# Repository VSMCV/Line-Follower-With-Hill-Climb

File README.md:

# Line-Follower-With-Hill-Climb
Hardware design and software files for a PID line follower robot with Hill Climb tuning

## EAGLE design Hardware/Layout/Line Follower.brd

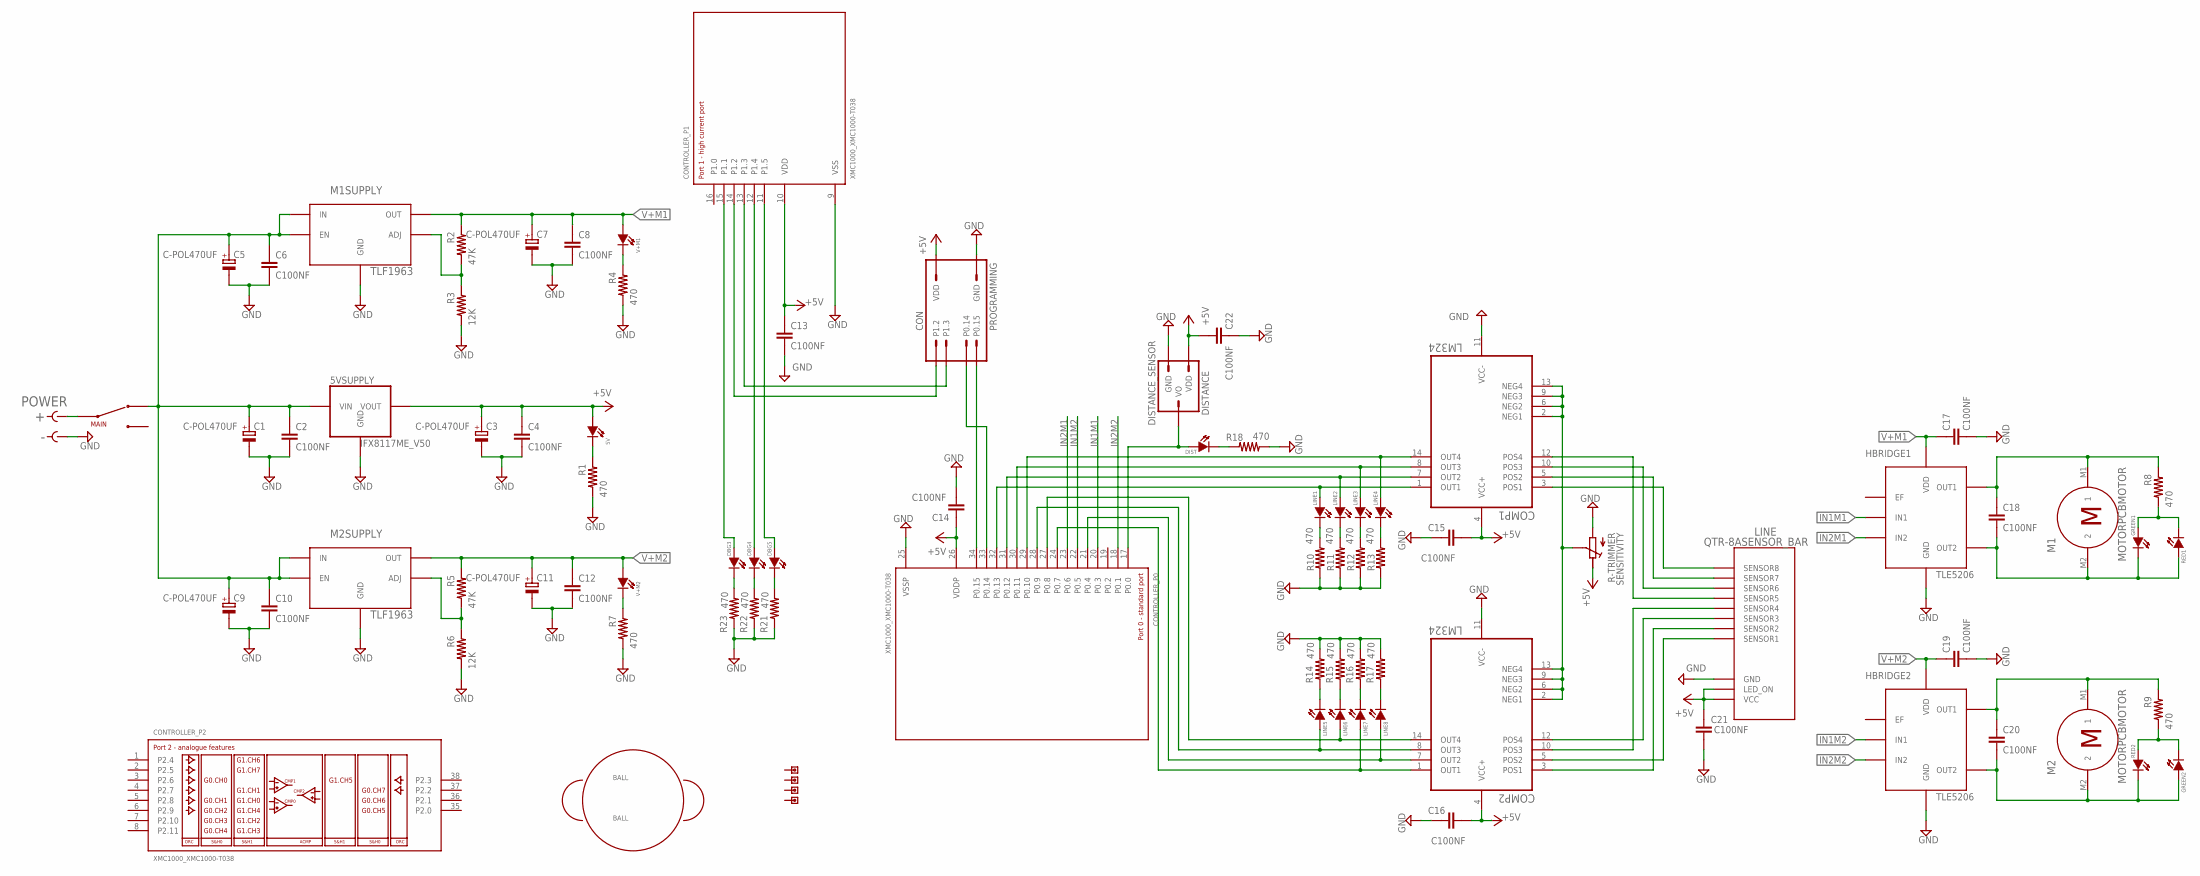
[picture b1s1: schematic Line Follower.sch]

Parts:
5V: LED; CHIPLED_1206
5VSUPPLY: IFX8117ME_V50; INF-PG-SOT223_SC-73_M_1PRIMARY
BALL: BALL
C1, C3, C5, C7, C9, C11: C-POL470UF; E3,5-8
C2, C4, C6, C8, C10, C12, C13, C14, C15, C16, C17, C18, C19, C20, C21, C22: C100NF; C1206
COMP1, COMP2: LM324; SO14
CON: PROGRAMMING; MA05-2
CONTROLLER: XMC1000_XMC1000-T038; XMC1000_P-TSSOP38-9
DBG3, DBG4, DBG5: LED; CHIPLED_1206
DIST: LED; CHIPLED_1206
DISTANCE: DISTANCE_SENSOR; MA03-2
GREEN1, GREEN2: LED; CHIPLED_1206
HBRIDGE1, HBRIDGE2: TLE5206; INF-PG-TO263-7-1_L_1PRIMARY
LINE: QTR-8ASENSOR_BAR; QTR-8A
LINE1, LINE2, LINE3, LINE4, LINE5, LINE6, LINE7, LINE8: LED; CHIPLED_1206
M1, M2: MOTORPCBMOTOR; MICRO-MOTOR
M1SUPPLY, M2SUPPLY: TLF1963; INF-PG-TO252-5-11_L_1PRIMARY
MAIN: SWITCH1OFF2; MS111
POWER: PWRCONCON1; PWRCON
R1, R4, R7, R8, R9, R10, R11, R12, R13, R14, R15, R16, R17, R18, R21, R22, R23: 470; R1206
R2, R5: 47K; R1206
R3, R6: 12K; R1206
RED1, RED2: LED; CHIPLED_1206
SENSITIVITY: R-TRIMMER; TRIMMER
U$2, U$3, U$4, U$5: SPACER; SPACERS_M3
V+M1, V+M2: LED; CHIPLED_1206

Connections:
+5V: 5V.A, 5VSUPPLY.2 (VOUT), 5VSUPPLY.4 (VOUT), C3.+, C4.1, C13.1, C14.2, C15.2, C16.2, C21.1, C22.1, COMP1.4 (VCC+), COMP2.4 (VCC+), CON.5 (VDD), CON.6 (VDD), CONTROLLER.10 (VDD), CONTROLLER.26 (VDDP), DISTANCE.1 (VDD), LINE.P$2 (LED_ON), LINE.P$4 (VCC), SENSITIVITY.2 (E)
GND: 5VSUPPLY.1 (GND), C1.-, C2.2, C3.-, C4.2, C5.-, C6.2, C7.-, C8.2, C9.-, C10.2, C11.-, C12.2, C13.2, C14.1, C15.1, C16.1, C17.2, C19.2, C21.2, C22.2, COMP1.11 (VCC-), COMP2.11 (VCC-), CON.3 (GND), CON.4 (GND), CON.9 (GND), CON.10 (GND), CONTROLLER.9 (VSS), CONTROLLER.25 (VSSP), DISTANCE.3 (GND), DISTANCE.4 (GND), DISTANCE.5 (GND), DISTANCE.6 (GND), HBRIDGE1.4 (GND), HBRIDGE1.8 (GND), HBRIDGE2.4 (GND), HBRIDGE2.8 (GND), LINE.P$6 (GND), LINE.P$8 (GND), LINE.P$10 (GND), LINE.P$12 (GND), LINE.P$14 (GND), LINE.P$16 (GND), M1SUPPLY.3 (GND), M2SUPPLY.3 (GND), POWER.-, R1.1, R3.1, R4.1, R6.1, R7.1, R10.2, R11.2, R12.2, R13.2, R14.2, R15.2, R16.2, R17.2, R18.1, R21.1, R22.1, R23.1, SENSITIVITY.1 (A)
IN1M1: CONTROLLER.20 (P0.3), HBRIDGE1.3 (IN1)
IN1M2: CONTROLLER.22 (P0.5), HBRIDGE2.3 (IN1)
IN2M1: CONTROLLER.23 (P0.6), HBRIDGE1.5 (IN2)
IN2M2: CONTROLLER.18 (P0.1), HBRIDGE2.5 (IN2)
unnamed: MAIN.P$2 (COM), POWER.+
unnamed: C20.2, GREEN2.A, HBRIDGE2.7 (OUT2), M2.M2 (2), RED2.C (K)
unnamed: 5V.C (K), R1.2
unnamed: CON.1 (P0.15), CONTROLLER.34 (P0.15)
unnamed: CON.2 (P0.14), CONTROLLER.33 (P0.14)
unnamed: CON.7 (P1.3), CONTROLLER.13 (P1.3)
unnamed: CON.8 (P1.2), CONTROLLER.14 (P1.2)
unnamed: COMP1.2 (NEG1), COMP1.6 (NEG2), COMP1.9 (NEG3), COMP1.13 (NEG4), COMP2.2 (NEG1), COMP2.6 (NEG2), COMP2.9 (NEG3), COMP2.13 (NEG4), SENSITIVITY.3 (S)
unnamed: COMP1.3 (POS1), LINE.P$15 (SENSOR8)
unnamed: COMP1.5 (POS2), LINE.P$13 (SENSOR7)
unnamed: COMP1.10 (POS3), LINE.P$11 (SENSOR6)
unnamed: COMP1.12 (POS4), LINE.P$9 (SENSOR5)
unnamed: COMP2.5 (POS2), LINE.P$1 (SENSOR1)
unnamed: COMP2.3 (POS1), LINE.P$3 (SENSOR2)
unnamed: COMP2.12 (POS4), LINE.P$5 (SENSOR3)
unnamed: COMP2.10 (POS3), LINE.P$7 (SENSOR4)
unnamed: 5VSUPPLY.3 (VIN), C1.+, C2.1, C5.+, C6.1, C9.+, C10.1, M1SUPPLY.1 (EN), M1SUPPLY.2 (IN), M2SUPPLY.1 (EN), M2SUPPLY.2 (IN), MAIN.P$1 (1)
unnamed: M1SUPPLY.5 (ADJ), R2.1, R3.2
unnamed: R4.2, V+M1.C (K)
unnamed: M2SUPPLY.5 (ADJ), R5.1, R6.2
unnamed: R7.2, V+M2.C (K)
unnamed: GREEN1.A, R8.1, RED1.C (K)
unnamed: C18.2, GREEN1.C (K), HBRIDGE1.7 (OUT2), M1.M2 (2), RED1.A
unnamed: C18.1, HBRIDGE1.1 (OUT1), M1.M1 (1), R8.2
unnamed: C20.1, HBRIDGE2.1 (OUT1), M2.M1 (1), R9.2
unnamed: CONTROLLER.12 (P1.4), DBG4.A
unnamed: COMP1.14 (OUT4), CONTROLLER.29 (P0.10), LINE4.A
unnamed: COMP1.8 (OUT3), CONTROLLER.30 (P0.11), LINE3.A
unnamed: COMP1.7 (OUT2), CONTROLLER.31 (P0.12), LINE2.A
unnamed: COMP1.1 (OUT1), CONTROLLER.32 (P0.13), LINE1.A
unnamed: COMP2.1 (OUT1), CONTROLLER.24 (P0.7), LINE7.A
unnamed: COMP2.7 (OUT2), CONTROLLER.21 (P0.4), LINE8.A
unnamed: COMP2.8 (OUT3), CONTROLLER.28 (P0.9), LINE5.A
unnamed: COMP2.14 (OUT4), CONTROLLER.27 (P0.8), LINE6.A
unnamed: CONTROLLER.17 (P0.0), DIST.A, DISTANCE.2 (VO)
unnamed: LINE1.C (K), R10.1
unnamed: LINE2.C (K), R11.1
unnamed: LINE3.C (K), R12.1
unnamed: LINE4.C (K), R13.1
unnamed: LINE5.C (K), R14.1
unnamed: LINE6.C (K), R15.1
unnamed: LINE7.C (K), R16.1
unnamed: LINE8.C (K), R17.1
unnamed: DIST.C (K), R18.2
unnamed: CONTROLLER.15 (P1.1), DBG3.A
unnamed: CONTROLLER.11 (P1.5), DBG5.A
unnamed: DBG5.C (K), R21.2
unnamed: DBG4.C (K), R22.2
unnamed: DBG3.C (K), R23.2
unnamed: GREEN2.C (K), R9.1, RED2.A
V+M1: C7.+, C8.1, C17.1, HBRIDGE1.6 (VDD), M1SUPPLY.4 (OUT), R2.2, V+M1.A
V+M2: C11.+, C12.1, C19.1, HBRIDGE2.6 (VDD), M2SUPPLY.4 (OUT), R5.2, V+M2.A

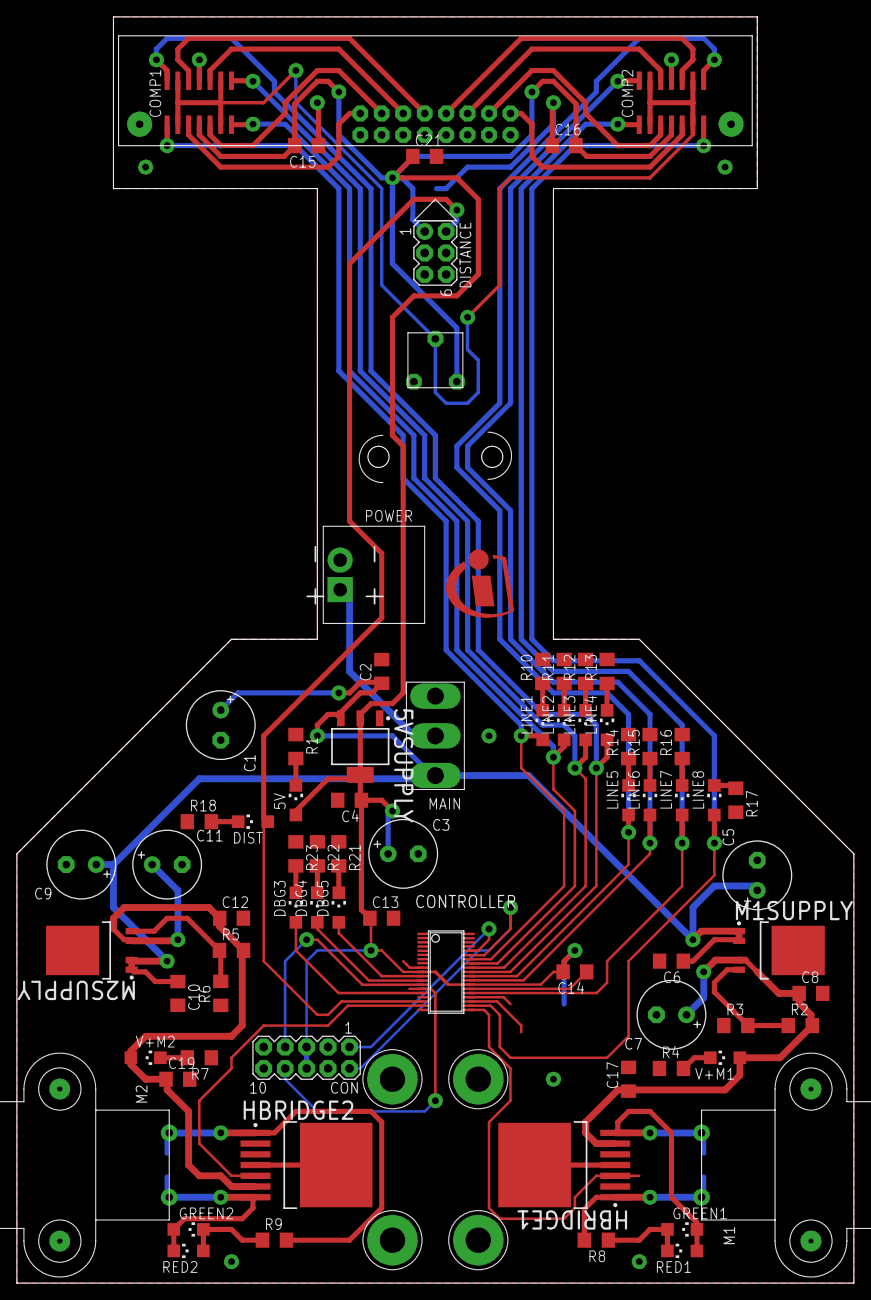
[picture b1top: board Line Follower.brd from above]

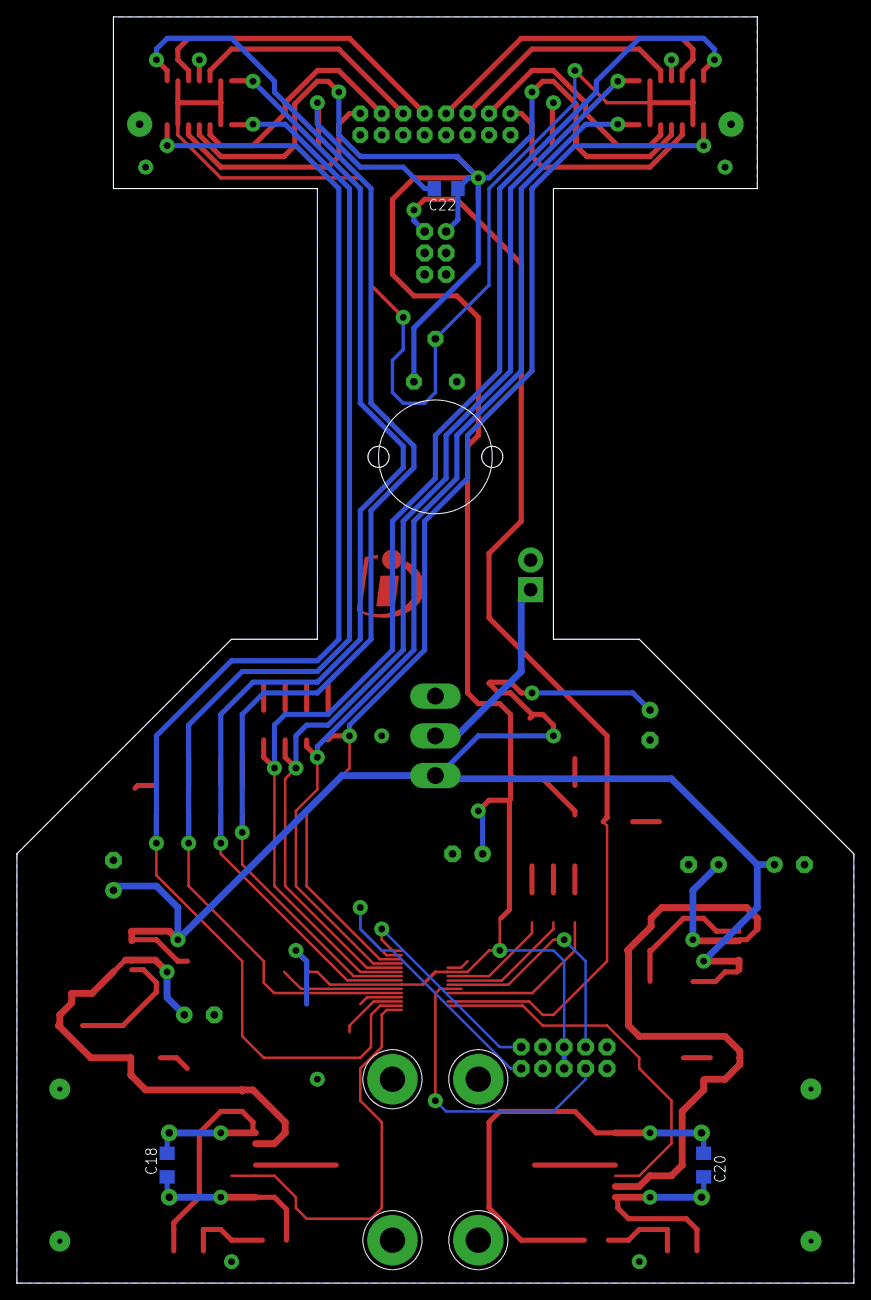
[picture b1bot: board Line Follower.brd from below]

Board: 2 copper layers, 99.1 x 149.9 mm, 84 parts (4 on the bottom side), 58 nets.

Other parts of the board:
U$1: INFINEON_LOGO_INFINEON_ICON_8

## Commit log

2017-09-07 initial
2017-09-07 software
2019-01-10 Add files via upload
    add layout pic
2019-01-10 Add schematic pic
2019-01-10 Add layout pic
